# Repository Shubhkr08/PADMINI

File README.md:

# PADMINI

PADMINI is a very small 5 buttons MicroPad that is based on XIAO RP2040. I added regular days Shortcuts to it that would help me in my days to day work.
The 5 buttions are for Copy,Paste,Delete,ScreenShot and Full Brightness. The PCB way design and made in kicad and 3d case was done in Fusion. I followed the Guild from HackClub which helped me a lot to process with this project. I did the farmware in circuit Python and KMK. It was Great working on this project.
## 🧾 Bill of Materials (BOM)

**#**
1 x XIAO RP2040<br>
**#**
5 x MX-Style switches <br>
**#**
5 x Blank DSA keycaps<br>
**#**
4 x  M3x16mm screws <br>
**#**
4 x  M3x5mx4mm heatset inserts <br>

<br><br>
**Schematic**

<br><br>
**PCB**<br>

<br><br>
**Case**<br>

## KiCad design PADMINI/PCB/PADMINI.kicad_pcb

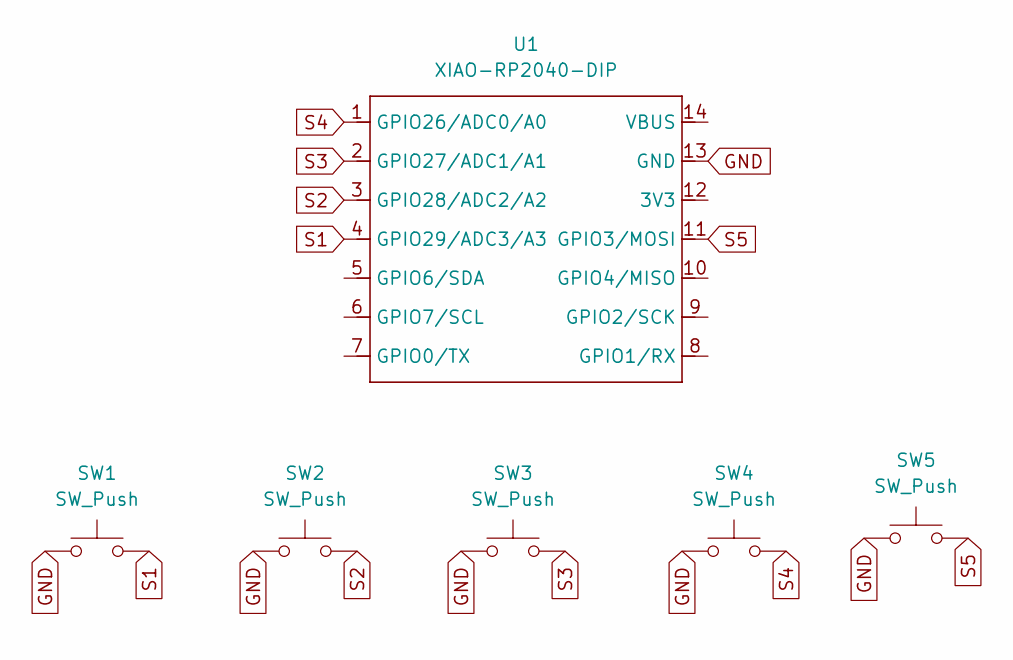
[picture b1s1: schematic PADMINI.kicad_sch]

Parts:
SW1, SW2, SW3, SW4, SW5: SW_Push; SW_Cherry_MX_1.00u_PCB
U1: XIAO-RP2040-DIP

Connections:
GND: SW1.1, SW2.1, SW3.1, SW4.1, SW5.1, U1.13 (GND)
S1: SW1.2, U1.4 (GPIO29/ADC3/A3)
S2: SW2.2, U1.3 (GPIO28/ADC2/A2)
S3: SW3.2, U1.2 (GPIO27/ADC1/A1)
S4: SW4.2, U1.1 (GPIO26/ADC0/A0)
S5: SW5.2, U1.11 (GPIO3/MOSI)

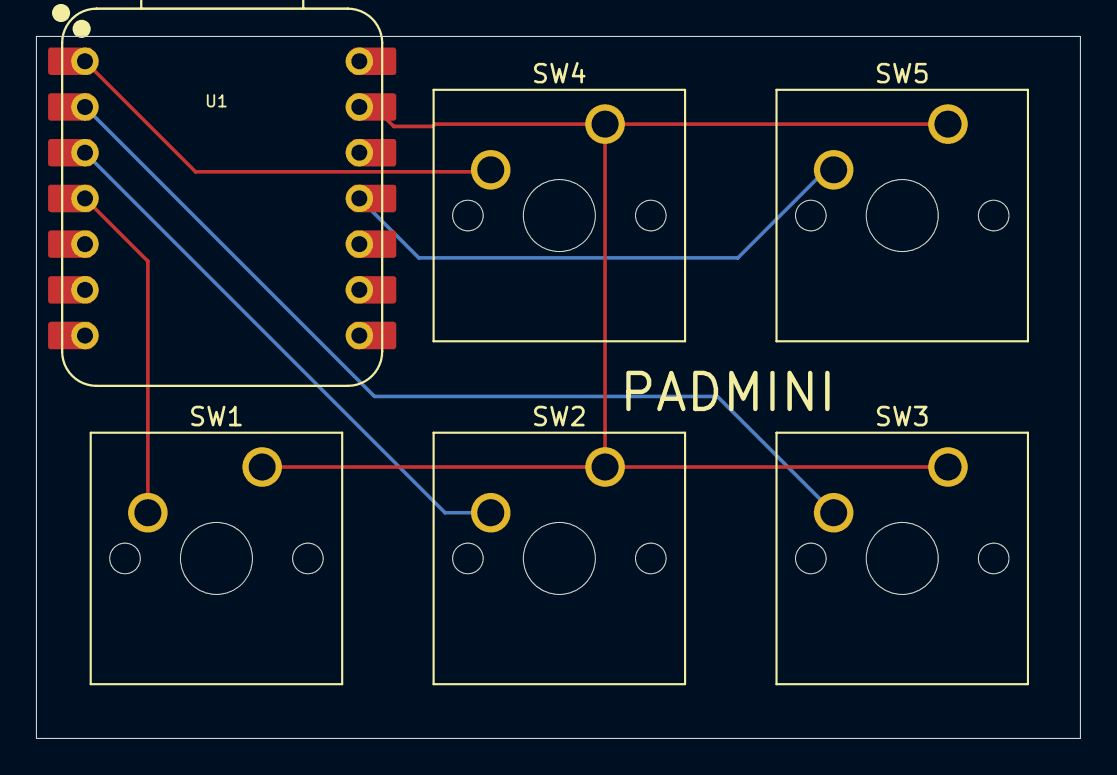
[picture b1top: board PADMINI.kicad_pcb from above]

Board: 2 copper layers, 58.0 x 39.0 mm, 6 parts (0 on the bottom side), 6 nets.
